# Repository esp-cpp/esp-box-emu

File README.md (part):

# esp-box-emu

<table style="padding:10px">
    <tr>
        <td></td>
        <td></td>
    </tr>
</table>

> A pocket-sized, Game Boy-style retro **emulation handheld** built around the
> ESP32-S3-BOX. Drop in a micro-SD card of ROMs and play NES, Game Boy / Color,
> Sega, MSX, and Genesis games — plus a full-speed port of **Doom** — on hardware
> you can 3D print and build yourself.

https://github.com/user-attachments/assets/2d3da6ea-2e80-42c3-bbd6-5a2c59601201

<!-- markdown-toc start - Don't edit this section. Run M-x markdown-toc-refresh-toc -->
**Table of Contents**

- [esp-box-emu](#esp-box-emu)
  - [Overview](#overview)
  - [Emulators](#emulators)
  - [Gallery](#gallery)
  - [Quick Start — Play It](#quick-start--play-it)
  - [Web Console](#web-console)
  - [Build the Hardware](#build-the-hardware)
  - [Build the Firmware](#build-the-firmware)
  - [ROMs and SD Card Setup](#roms-and-sd-card-setup)
    - [Boxart images](#boxart-images)
    - [metadata.csv format](#metadatacsv-format)
  - [Features and Roadmap](#features-and-roadmap)
  - [References and Inspiration](#references-and-inspiration)
  - [License](#license)

<!-- markdown-toc end -->

## Overview

The ESP-BOX-EMU turns an [ESP32-S3-BOX or
ESP32-S3-BOX-3](https://github.com/espressif/esp-box) into a handheld retro game
console. A custom add-on board and 3D-printed shell wrap the BOX in a Game Boy
Color form factor — real d-pad and buttons, battery, haptics, and a micro-SD
slot — and the firmware runs a stack of emulators behind a polished LVGL
interface with boxart, save states, and settings.

**Highlights**

- 🎮 **Six systems + Doom** — NES, Game Boy / Color, Sega Master System / Game
  Gear, Sega Genesis, and MSX 1/2 emulators, plus a full-speed **Doom** port —
  all with sound.
- 🧬 **Full-speed Genesis** — a custom **dual-core** port of gwenesis splits the
  emulation across both of the ESP32-S3's cores (CPU + video on one, the sound
  unit on the other) for full-speed Sega Genesis / Mega Drive *with* audio.
- ⚡ **No reboots** — every core and game loads on demand right from the menu, so
  you can jump between titles and even different systems without ever restarting
  the device.
- 🕹️ **Real controls** — d-pad, A/B/X/Y, Start/Select and volume buttons in a
  familiar Game Boy Color layout; the emulator is auto-selected from the ROM
  file extension.
- 💾 **Load from SD** — keep ROMs, boxart, and save states on a micro-SD card,
  and mount the card over USB-C as a mass-storage drive (TinyUSB MSC).
- 💤 **Save anywhere** — up to 5 save slots per game, each with an
  auto-generated screenshot shown in the load menu.
- 🔋 **Portable** — 1000 mAh LiPo battery with USB-C charging.
- 📳 **Haptics** — LRA haptic feedback (DRV2605), including in-game effects in
  Doom (weapon fire, taking damage, pickups, and more).
- 🖼️ **Polished UI** — LVGL menus for ROM select (with boxart) and settings
  (sound, brightness, display scaling, haptics), designed in Squareline Studio.
- 🌐 **Web console** — plug into a computer and Chrome or Edge offers a control
  panel: watch and play the screen, manage games and boxart, browse the SD
  card, change settings, and update the firmware, with nothing to install.
- 🛠️ **Fully open hardware** — 3D-printable GBC-style case and an open PCB
  (Fusion/Eagle **and** [atopile](https://atopile.io) + [KiCad](https://kicad.org)),
  all included in this repo.

## Emulators

The right emulator is chosen automatically from each ROM's file extension, and
games load on demand **straight from the menu — no reboot required**. Pick a
title, play, then drop back to the menu and launch a different game (or a
completely different system) without ever restarting the device. Every core runs
with audio, and several offer an **Unlocked mode** (toggle with the **X** button)
that removes the frame-rate cap for maximum speed.

| System | Core | Unlocked mode | Notes |
| --- | --- | :---: | --- |
| NES | [nofrendo](https://github.com/espressif/esp32-nesemu) | ✅ | D-Pad / A / B / Start / Select |
| Game Boy / Color | [gnuboy](https://github.com/rofl0r/gnuboy) | ✅ | D-Pad / A / B / Start / Select |
| Sega Master System / Game Gear | [smsplus](https://github.com/ekeeke/smsplus-gx) | ✅ | D-Pad / A / B / Start / Select |
| Sega Genesis / Mega Drive | [gwenesis](https://github.com/bzhxx/gwenesis) | — | Full speed with sound; 6-button pad (A→B, B→A, C→Y) |
| MSX 1 / 2 | [fmsx](https://fms.komkon.org/fMSX/) | — | D-Pad / A / B / Start / Select |
| Doom | [prboom](https://prboom.sourceforge.net/) | — | Full speed with audio **and haptic feedback** |
| Dark Forces | [The Force Engine](https://theforceengine.github.io/) (via [BSzili's Amiga port](https://github.com/BSzili/TheForceEngine/tree/amiga)) | — | Software renderer, iMuse sound effects and OPL3 music; see [Dark Forces setup](#dark-forces-setup) |
| PICO-8 | [femto8](https://github.com/benbaker76/femto8) | — | `.p8` and `.p8.png` carts; D-Pad, A/Y = O, B/X = X, START = PICO-8 pause menu; save states; cartdata saves to `pico8/cdata/`; see [PICO-8 setup](#pico-8-setup) |

Every core is a submodule ([esp-cpp/nofrendo](https://github.com/esp-cpp/nofrendo),
[gnuboy](https://github.com/esp-cpp/gnuboy), [smsplus](https://github.com/esp-cpp/smsplus),
[gwenesis](https://github.com/esp-cpp/gwenesis), [fmsx](https://github.com/esp-cpp/fmsx),
[prboom](https://github.com/esp-cpp/prboom), [TheForceEngine](https://github.com/esp-cpp/TheForceEngine),
[femto8](https://github.com/esp-cpp/femto8)): the core plus its `port/` glue to
`BoxEmu`, shared with [tab5-emu](https://github.com/esp-cpp/tab5-emu). Each
`components/<core>/CMakeLists.txt` here is the board's wrapper for it
(requirements, compile flags, linker fragment).

> 🧬 **Full-speed Genesis on the S3.** The Genesis core ships with a custom
> **dual-core** modification of gwenesis that spreads the workload across both of
> the ESP32-S3's CPU cores: **core 0** runs the 68000 CPU and VDP (video), while
> **core 1** runs the sound unit (Z80 + YM2612 FM synth + PSG). Sound-chip writes
> are queued and applied in order on core 1, which lets Genesis / Mega Drive
> games run at full speed *with* audio — something a single core can't keep up
> with.

<details>
<summary><strong>Doom controls and haptics</strong></summary>

**Controls:** **A** fire / enter · **B** strafe / backspace · **X** use ·
**Y** weapon toggle · **START** escape · **SELECT** map.

**Haptic feedback** is triggered when you fire a weapon (varies by weapon), take
damage (scaled to the health/armor lost), interact with something (e.g. a door),
or pick up a weapon, ammo, health, armor, a power-up, or a key / card.
</details>

<details>
<summary><strong>Dark Forces controls</strong></summary>

**In a mission:** **D-pad** move / turn · **A** fire · **B** jump · **X** use ·
**Y** next weapon · **START** escape menu. Hold **SELECT** as a modifier:
**SELECT + Left/Right** strafe · **SELECT + Down** crouch · **SELECT + Up**
automap · **SELECT + A** secondary fire · **SELECT + B** headlamp ·
**SELECT + X** gas mask · **SELECT + Y** previous weapon · **SELECT + START**
night vision. Running is always on.

**Menus, briefings and cutscenes:** the **D-pad** moves a virtual mouse cursor,
**A** clicks, **START** is Enter, **B** is Escape (skips cutscenes) and **Y** is
Space. Quitting from the game's escape menu returns to the emulator menu.

**Typing an agent name:** hold **SELECT**: **Right** adds a letter, **Up/Down**
change the last letter, **Left** deletes it; release SELECT and press **START**
to confirm.

The emulator's own pause menu (touch button or START+SELECT) still works for
video scaling and save slots; save slots only work while in a mission.
</details>

## Gallery

https://github.com/esp-cpp/esp-box-emu/assets/213467/3b77f6bd-4c42-417a-9eb7-a648f31b4008

https://github.com/esp-cpp/esp-box-emu/assets/213467/a3d18d03-c6a1-4911-89d1-e18119e8cc03

## Quick Start — Play It

Already have the add-on hardware (or an ESP32-S3-BOX you want to flash)? You
don't need to build anything from source — a prebuilt one-time **programmer** is
published with every release.

1. Download the `programmer` for your OS (`windows`, `macos`, or `linux`) from
   the latest [releases page](https://github.com/esp-cpp/esp-box-emu/releases).
2. Unzip it.
3. Run it: double-click the `.exe` on Windows, or run it from a terminal on
   macOS / Linux, e.g.:

   ```sh
   ./esp-box-emu_programmer_v1.0.0_macos.bin
   ```

   (The version in the filename matches the release you downloaded.)

Then [set up a micro-SD card](#roms-and-sd-card-setup) with your ROMs and you're
ready to play.

## Web Console

**Plug the emulator into a computer and it hands you a control panel.**
Connect the ESP-BOX-EMU's USB-C port to a computer running Chrome or Edge and
the browser pops up a notification pointing at
**[esp-cpp.github.io/esp-box-emu](https://esp-cpp.github.io/esp-box-emu/)**,
the firmware's WebUSB landing page. Click it, pick the emulator, and you're in:
no drivers, no app, no serial terminal. Watch the game being played,
take a screenshot, add a new game with its boxart, or update the firmware,
all from a browser tab.

What you can do from each tab:

- 📊 **Dashboard**: what's running right now (with its boxart), live frame-rate
  and memory graphs, the firmware and partition it booted from, why it last
  reset, and a button that hands the SD card to your PC as a USB drive.
- 🖥️ **Screen**: grab the game's (or the launcher's) screen, or turn on
  **Live** to keep it updating, and save it as a PNG. Play with the on-screen
  controller or your keyboard (arrows, Z / X / A / S, Enter = Start), save and
  load states in any slot, or quit the game.
- 📚 **Library**: every game on the card, grouped by console with its boxart
  and a game count per console. Search, filter by console (and, if you like,
  filter the handheld's launcher the same way), start any game with **Play**,
  or **Add a game**: drop in the ROM and a cover and the page uploads both and
  adds the line to `metadata.csv` for you. **Remove** takes one out again.
- 📁 **Files**: browse the SD card, download files, upload by drag and drop,
  create folders and delete things (handy for copying save states off the card).
- ⚙️ **Settings**: volume, mute, brightness, video scaling, resume last save
  and the haptic effect. The handheld's own menu shows each change right away,
  and it's saved to the card a moment later.
- 🔧 **System**: chip, flash, PSRAM, heap, ESP-IDF version, OTA state and the
  services on the link; restart the emulator (or into download mode for
  `idf.py flash`), and **Update firmware**, which restarts into the updater and
  opens the espp OTA console to send a new `build/esp-box-emu.bin`.
- 📜 **Console**: the device's log over Web Serial (pick the console's port),
  with a line filter, auto-follow, and save to a file.

**How it works:** the firmware's composite USB device includes a vendor
(WebUSB) interface that carries the same request/response link as
[`tools/emulink`](./tools/emulink), plus a USB descriptor that names the
landing page, which is how the browser knows where to send you. The page is
plain HTML, CSS and JavaScript modules in [`web/`](./web) (no build step),
published to GitHub Pages from `main`, and it talks to the device directly
from your browser; nothing goes through a server. Only one program can use the
link at a time, so close `emulink` (or the page) before switching between them.

Hacking on the page? Serve it locally with
`python3 -m http.server -d web 8000` and open http://localhost:8000 (WebUSB
needs https or localhost). See [`web/README.md`](./web/README.md) for the
details.

## Build the Hardware

The add-on is designed to match the Game Boy Color form factor and reuse GBC
button plastics and silicone membranes for an authentic feel. The shell is meant
to be 3D printed (PLA or PETG on a Prusa i3 mk3+) and assembled with M3 screws.

**Case / mechanical** — printable files are in [./mcad](./mcad) or on
[Printables](https://www.printables.com/model/396931-esp-box-emu). CAD is on
[Fusion 360 (free viewer)](https://a360.co/3le5oCQ):

**Electronics** — schematic and layout files are in [./ecad](./ecad), provided
as both Fusion/Eagle files and [atopile](https://atopile.io) +
[KiCad](https://kicad.org) sources. You can also order the board directly:

**GBC replacement buttons / membranes** used for a good play feel:

- [Silicone pads for Game Boy Color (1)](https://funnyplaying.com/collections/product/products/gbc-replacement-silicone-pads)
- [Silicone pads for Game Boy Color (2)](https://www.retromodding.com/products/game-boy-color-silicone-pads)
- [Game Boy Color button plastics](https://funnyplaying.com/collections/product/products/cgb-custom-buttons?variant=39333911920701)

## Build the Firmware

This repo uses submodules, so clone it recursively:

```sh
git clone --recurse-submodules git@github.com:esp-cpp/esp-box-emu
```

If you already cloned it non-recursively (or forgot the flag), pull the
submodules with:

```sh
git submodule update --init --recursive
```

Then build, flash, and open the serial monitor with [ESP-IDF](https://docs.espressif.com/projects/esp-idf/en/latest/esp32s3/get-started/index.html):

```sh
idf.py -C updater build   # once: the updater app, which goes in ota_1
idf.py -p PORT flash monitor
```

The updater (`updater/`) is what over-USB updates (`tools/emulink`) reboot
into, and what a bad update rolls back to, so build it before the first
flash: the emulator's `idf.py flash` then writes both. After that, updates
can go over USB with `emulink ota`.

Replace `PORT` with your board's serial port. To exit the monitor, type
`Ctrl-]`.

### Measuring performance and memory

The firmware prints greppable one-line reports on the serial console so a
captured play session doubles as a profile:

- `[mem] phase=boot|menu|launch|quit ...` — internal RAM / PSRAM free and
  largest free block at each phase, with `[mem] delta ...` lines at launch and
  quit relative to the menu (a non-zero delta after quitting is a leak or
  fragmentation).
- `[mem] block|region|task phase=...` — at boot and launch, every internal-RAM
  block above a threshold (labelled with the task whose stack it is), each
  registered heap region's used/free/largest, and every task's stack high-water
  mark (`stack_free_min`, repeated at quit after a full play session).
- `[genesis mem] NAME: N bytes -> INTERNAL|PSRAM` — where each big emulator
  buffer landed (the Genesis gets noticeably slower when its hot buffers fall
  back to PSRAM).
- `[genesis perf] fps=.. frame=..us 68k=..us vdp=..us convert=..us barrier=..us ...` —
  per-frame time breakdown averaged over the last 300 frames (~5 s): 68000,
  VDP render, RGB565 conversion, time core 0 spends waiting for the core-1
  sound unit, present/audio, pacing sleep, `late=`/`skipped=`/`dropped=`
  frame counts (skipped = emulated without rendering because the panel could
  not show the frame), `blit=` (video task time per displayed frame), the
  core-1 sound unit's own frame time, and Z80 counters (`irq=` V-ints taken,
  `busreq=`, `halted=` scanline slices lost to a held bus, `wto=` handshake
  timeouts, `ymw=` Z80→YM2612 writes). Compile with `GENESIS_PERF=0` to
  remove it.
- `[display] lcd spi clock: N Hz` — the clock the LCD SPI device actually got
  (the ESP32-S3 can only divide 80 MHz by integers, so a 60 MHz request runs
  at 40 MHz: 320×240×16bpp is ~31 ms per frame, the panel's ~31 fps ceiling).

Capture and summarise a session (performance PRs should include a before/after
from the same game and the same ~1 minute of play):

```sh
python tools/serial_capture.py PORT --out before.log --until "delta phase=quit"
# ... flash the change, play the same section again ...
python tools/serial_capture.py PORT --out after.log --until "delta phase=quit"
python tools/perf_report.py before.log after.log
```

`perf_report.py` prints each run's launch/quit memory, buffer placement, and
the perf-line averages side by side with deltas.

## ROMs and SD Card Setup

Format a micro-SD card as **FAT** and add your ROMs (`.nes`, `.gb`, `.gbc`, …),
boxart images (`.jpg`), and a `metadata.csv` file (see the example
[metadata.csv](./metadata.csv)).

### Boxart images

Boxart displays best at 100 px wide. The
[./boxart/source/resize.bash](./boxart/source/resize.bash) script resizes every
`.jpg` in `boxart/source` to 100 px wide (preserving aspect ratio) and writes the
results to the `boxart` folder. Copy those onto the SD card and reference them
from your metadata file.

### Dark Forces setup

Dark Forces is played with the original (purchased) game data; the engine does
not include it. Copy the DOS install files onto the SD card into a single
folder, for example `darkforces/`:

```
darkforces/DARK.GOB
darkforces/SOUNDS.GOB
darkforces/SPRITES.GOB
darkforces/TEXTURES.GOB
darkforces/LFD/*.LFD       (menus, briefings and cutscenes)
```

Then reference `DARK.GOB` from `metadata.csv`:

```csv
darkforces/DARK.GOB, boxart/darkforces.jpg, Star Wars: Dark Forces
```

Settings (`settings.ini`) and agent / save files are written to the same folder.

### PICO-8 setup

PICO-8 carts are plain `.p8` text files or `.p8.png` cartridge images. Put them
in a folder on the card (for example `pico8/`) and reference them from
`metadata.csv`:

```csv
pico8/celeste.p8, boxart/celeste.jpg, Celeste Classic
```

Carts that use `cartdata()` save to `pico8/cdata/`. The 128x128 screen shows
1:1 in the "original" video mode and scaled to 240x240 in "fit". Multi-cart
games that `load("#id")` their other carts work when those carts sit in the
same folder as `id.p8.png` / `id.p8`.

What to expect: the Lua interpreter runs at roughly 1.3M instructions per
second on the S3 (its heap lives in PSRAM), enough for carts of Celeste's
weight at full speed, but CPU-heavy carts close to PICO-8's limit run at a
few frames per second. Save states work (the cart's Lua heap and PICO-8
RAM are snapshotted between frames); carts' own `cartdata()` saves are kept
separately; there is no mouse or keyboard.

### metadata.csv format

Each line maps a ROM to its boxart and display name:

```csv
<rom filename>, <rom boxart filename>, <rom display name>
```

Example:

```csv
mario.nes, boxart/mario.jpg, Mario Bros.
super_mario_1.nes, boxart/super_mario_bros_1.jpg, Super Mario Bros.
super_mario_3.nes, boxart/super_mario_bros_3.jpg, Super Mario Bros. 3
zelda.nes, boxart/zelda1.jpg, The Legend of Zelda
zelda_2.nes, boxart/zelda2.jpg, The Legend of Zelda 2: the Adventure of Link
mega_man.nes, boxart/megaman1.jpg, MegaMan
metroid.nes, boxart/metroid1.jpg, Metroid
pokemon_blue.gb, boxart/pokemon_blue.jpg, Pokemon Blue
pokemon_red.gb, boxart/pokemon_red.jpg, Pokemon Red
pokemon_yellow.gbc, boxart/pokemon_yellow.jpg, Pokemon Yellow
links_awakening.gb, boxart/tloz_links_awakening.jpg, The Legend of Zelda: Link's Awakening
links_awakening.gbc, boxart/tloz_links_awakening_dx.jpg, The Legend of Zelda: Link's Awakening DX
```

## Features and Roadmap

A checklist of what's implemented and what's still in progress.

**Emulation**

- [x] Auto-select emulator by ROM extension: NES, GB/GBC, SMS/GG, MSX, Genesis, Doom, Dark Forces, PICO-8
- [x] On-demand core loading — every emulator and game loads at runtime with no reboot needed to switch games or systems
- [x] Custom **dual-core Genesis** (gwenesis): 68000 + VDP on one ESP32-S3 core, sound unit (Z80 + YM2612 + PSG) on the other, for full-speed audio and gameplay
- [x] Doom haptic feedback :rocket:
- [x] Save state (with automatic save-screenshot creation to the SD card)
- [x] Load state — up to 5 slots per game, with save-screenshot previews
- [x] Shared-memory system so many emulators can be built in together while keeping their hot state in fast internal RAM
- [x] Dark Forces (The Force Engine port; software renderer with sound and music)
- [ ] SNES emulator (WIP)

**User interface**

- [x] LVGL ROM-select menu with boxart and title, navigable by controller
- [x] Games grouped by console: left / right jump to the previous / next
  console, and the console in the header (tap it, or press X) opens a picker
  that shows only one console's games (outlined while filtered; `emulink
  filter <console>` over USB)
- [x] LVGL settings menu (volume, video, haptics) and in-game pause menu
- [x] GUI data (titles + boxart) loaded from the [metadata file](./metadata.csv)
- [x] Squareline Studio source for the LVGL boilerplate ([SLS files](./squareline), [generated files](./components/gui/generated))

**Video and audio**

- [x] Emulator framebuffers in SPIRAM, with queued screen transfers for maximum draw speed
- [x] Video scaling with ORIGINAL, FIT, and FILL display modes
- [x] Audio output over I2S via the es8311 codec ([codec component](./components/codec))
- [x] Mute button toggles audio while a ROM is running
- [x] Haptic feedback via a DRV2605-driven LRA
- [ ] Decorative graphics in the black borders during NES / GB/C emulation (WIP)

**Storage and input**

- [x] micro-SD (FAT) filesystem over SPI
- [x] TinyUSB MSC device to expose the SD card to an attached USB host
- [x] Memory-mapping of the selected ROM from storage into a raw data partition (SPI flash)
- [x] D-pad + A/B/X/Y + Start/Select input (MCP23x17 on v0 hardware, AW9523 on v1)
- [x] Touchscreen input ([tt21100 component](./components/tt21100))

**Hardware**

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
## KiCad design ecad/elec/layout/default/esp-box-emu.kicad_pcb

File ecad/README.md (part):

# ESP-BOX-EMU ecad

This folder contains the electronic design of the ESP-BOX-EMU.

The ESP-BOX-EMU contains a single circuit board with the following components:
- USB-C connector
- Conductive / Membrane switches for d-pad, abxy, and start/select buttons which mate with GBC membranes and buttons
- Tactile switches for Volume +/-
- RED LED for charging indication
- DRV2605L haptic driver
- JST-PH connector for the LiPo battery
- AW9523 I/O expander
- MCP73831 LiPo charger
- MAX17048 LiPo state-of-charge monitor (I2C)
- MicroSD card slot
- TPS63020 5V buck-boost converter (battery -> 5V for the box)

These features are supported in two different versions of the electronics, targeting:
- ESP32-S3-Box
- ESP32-S3-Box-3

## Layout of this folder

- `elec/src/` - atopile sources (modern atopile >= 0.15 syntax)
- `elec/src/parts/` - atomic parts (auto-generated from LCSC plus local
  custom parts for the GBC membranes/buttons, board outlines and edge fingers)
- `elec/layout/` - KiCad layouts, one folder per build (netlist-synced by
  `ato build`; placement/routing edits are preserved)
- `scripts/` - layout automation (MCAD position export, scripted placement,
  base/connector layout sync)
- `Box Electronics v*.sch/brd`, `Box-3 Electronics v*.sch/brd` - the
  Fusion 360 / Eagle design the boards were actually manufactured from

The pre-migration atopile 0.2 sources, the old shared footprint library and
the old routed KiCad-6 boards were removed after the 0.15 migration; they
are available in git history (pre-2026-07) if ever needed.

## Setup

``` sh
# one time steps on your machine (any of these; uv shown)
uv tool install --python 3.14 atopile
```

Dependencies (e.g. `atopile/ti-tps63020`) are fetched automatically into
`.ato/modules/` on first build; `ato add <package>` adds new ones.

## Build

``` sh
# build everything
ato build

# build for ESP32-S3-BOX
ato build -b box-emu

# build for ESP32-S3-BOX-3
ato build -b box-3-emu
```

### Offline build (atopile 0.16 service migration)

As part of atopile's 0.16 platform migration (services moving from
`*.atopileapi.com` / `packages.atopile.io` to `app.atopile.io`), the hosted
components-picker API used by the 0.15.x CLI
(`components.atopileapi.com`) was taken offline, and no public replacement
endpoint exists for the CLI yet. Until atopile publishes a CLI that speaks
to the new services, build via the local stand-in server, which answers
picker queries from the part data already pinned in this repo:

``` sh
scripts/ato-build-offline.sh                 # all targets
scripts/ato-build-offline.sh -b box-emu-base # one target
```

Two caveats:

- Footprints/symbols still come from `build/cache/parts/easyeda/` (or the
  still-alive EasyEDA API). If the cache is stale (>1 day old), refresh the
  `atopile_queried_at` stamps inside the cached `C*.json` files rather than
  hammering EasyEDA's rate limiter with re-downloads.
- The stand-in returns no part *attributes*, so builds rewrite the hidden
  parameter annotations in the layouts to the design constraints (e.g. a
  resistor annotated `10kΩ ±1%` from the real part data becomes `±5%` from
  the design). The picked LCSC parts, BOM and copper are unchanged; a
  normal online build will restore the exact annotations once the service
  returns.

## Continuous integration

`.github/workflows/atopile.yml` (official `atopile/setup-atopile@v2` action)
builds every target from the checked-in sources with
`ato build --keep-picked-parts --keep-net-names --keep-designators`, then
runs `scripts/canonicalize-boards.py --all` and fails if `git diff` shows
any change to `elec/layout` or `elec/src` -- i.e. the checked-in design
must be exactly reproducible. (We don't use `ato build --frozen`: atopile
0.15.x writes KiCad group member lists in nondeterministic order, which
makes frozen flaky; the canonicalize+diff check gives the same guarantee
robustly.) It then exports gerbers, pick & place, BOM, STEP, GLB and a
rendered PNG for `box-emu` and `box-3-emu` (`-t all -t 3d-image`), plus
top/bottom PDFs via the kicad-cli bundled in the atopile container.
Artifacts are uploaded per board and attached to releases as zips.

Two reproducibility rules this relies on:

- **Parts are pinned.** None of the part `.ato` files carry the
  `is_auto_generated` trait: atopile would otherwise re-download every
  picked part from the EasyEDA API on each build and *replace* the
  checked-in part directory whenever the API response differs (which it
  does between regions, over time, and during their frequent partial
  outages). Without the trait, atopile logs "not overwriting" and the
  repo stays the source of truth. To intentionally update a part, delete
  its directory and re-run `ato create part --search <LCSC>`.
- **After local layout sessions**, run `ato build` +
  `python3 scripts/canonicalize-boards.py --all` and commit the result,
  so CI's rebuild matches byte-for-byte.

The LCSC/EasyEDA API has multi-hour outages; build steps retry, but a
run during a hard outage will still fail at part picking -- just re-run
it later.

## Ordering / manufacturing notes

**Surface finish: order ENIG, not HASL.** The GBC button footprints expose
bare-copper interdigitated fingers that the carbon membrane pucks press
against. With HASL those fingers come back coated in solder (uneven, prone
to oxidation) and the buttons work poorly; with ENIG they come back flat
gold, which is the standard finish for carbon-contact keypads. This is a
per-order fab option (JLCPCB: "Surface Finish" -> "ENIG") and cannot be
enforced from the design files.

Related, already handled in the footprints: the buttons' four corner
connection pads are tented (copper-only, no paste, no mask opening), so
PCBA assembly applies no solder anywhere on the button contact areas. If
you regenerate or edit `GBC_*_BUTTON` footprints, keep the pads
`(layers "F.Cu")` only.

## Working on the KiCad layouts

Each build owns one board file: `elec/layout/<build>/<build>.kicad_pcb`
(KiCad 9+ format; there is no `.kicad_pro` — open the `.kicad_pcb` directly
in KiCad's PCB Editor). The `fp-lib-table` next to each board resolves all
footprints from the atomic parts in `elec/src/parts/`, so the boards are
self-contained as long as the repo layout is intact.

The `.ato` sources are the source of truth for everything electrical;
KiCad is only for placement and routing:

``` sh
# build a target and open its layout in KiCad in one step
ato build -b box-3-emu --open

# or open it manually
open "elec/layout/box-3-emu/box-3-emu.kicad_pcb"
```

The edit loop:

1. Change schematics by editing the `.ato` files (never add/remove
   components or change connectivity in KiCad — the next build will
   revert it).
2. Run `ato build -b <build>`. This syncs footprints and nets into the
   board file. Footprints are matched by their `atopile_address` property,
   so your existing placement and routing are preserved; new components
   appear stacked near the origin for you to place.
3. Place/route in KiCad and save. **Close the board (or at least save it)
   before the next `ato build`** — atopile rewrites the file on disk, and
   KiCad's PCB editor will not auto-reload; reopen the file after each
   build. A stale `~<name>.kicad_pcb.lck` file means KiCad still has it
   open.

Useful flags when iterating on layout: `--keep-designators`,
`--keep-net-names`, and `--keep-picked-parts` take those from the existing
PCB instead of regenerating them, and `--frozen` fails the build if the
PCB would change at all (good for CI).

Recovering from common accidents:

- **Deleted a footprint in KiCad?** Harmless to the design -- the `.ato`
  source is the source of truth, and the next `ato build -b <build>`
  re-adds it (near the origin; its placement is lost, its part gets
  re-picked). Restore known positions with `place-parts.py apply` if it
  was a mechanically-placed part. It's worth running
  `place-parts.py dump` into `positions.json` after every good layout
  session (and committing it) so *every* part's placement has a snapshot.
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
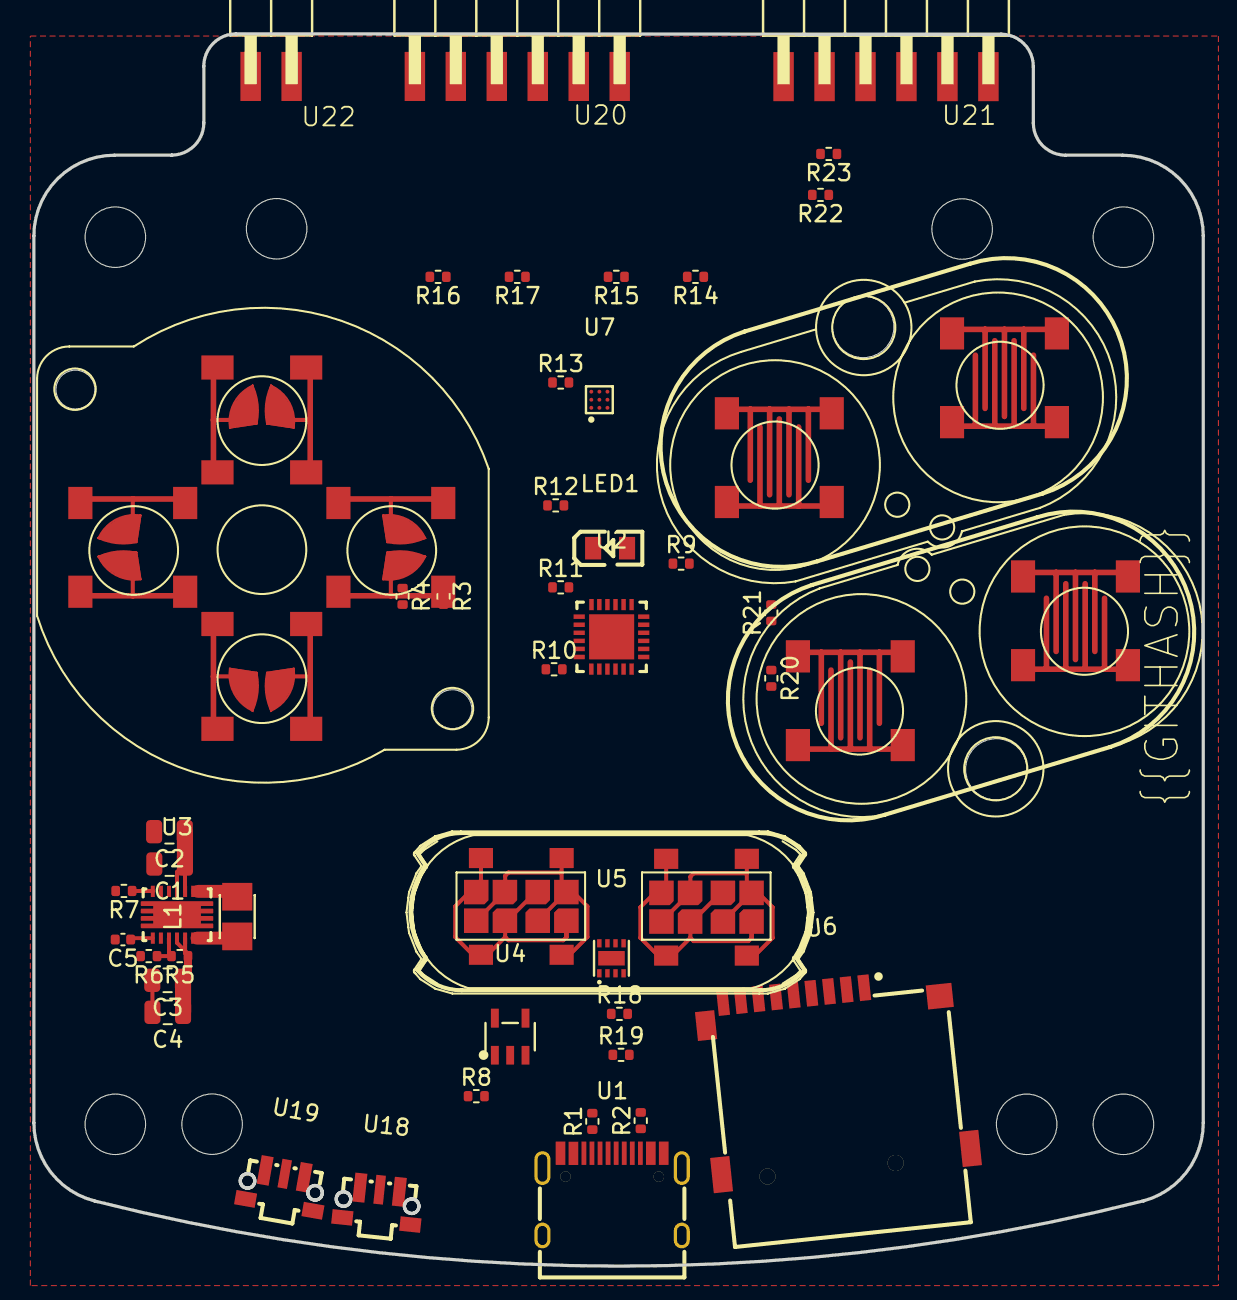
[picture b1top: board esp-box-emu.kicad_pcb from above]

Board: 2 copper layers, 72.5 x 76.4 mm, 64 parts (0 on the bottom side), 39 nets.

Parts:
@HOLE0, @HOLE1, @HOLE2, @HOLE3, @HOLE4, @HOLE5, @HOLE6, @HOLE7: (no value)
C1, C2, C3, C4: 25V 10uF X5R ±10% 0805 Multilayer Ceramic Capacit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; C0805
C5: 16V 100nF X7R ±10% 0402 Multilayer Ceramic Capaci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; C0402
L1: IND-SMD_L2.5-W2.0_WPN252012H
LED1: LED0805-R-RD
R1, R2: 62.5mW Thick Film Resistors 50V ±100ppm/℃ ±1% 4.7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; R0402
R3, R4, R10, R11, R12, R13, R14, R15, R16, R17, R18, R19, R20, R21: 62.5mW Thick Film Resistors 50V ±100ppm/℃ ±1% 10k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; R0402
R5: 62.5mW Thick Film Resistors 50V ±100ppm/℃ ±1% 243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; R0402
R6: 62.5mW Thick Film Resistors 50V ±100ppm/℃ ±0.5% 2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; R0402
R7: 62.5mW Thick Film Resistors 50V ±100ppm/℃ ±1% 1MΩ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; R0402
R8: 62.5mW Thick Film Resistors 50V ±100ppm/℃ ±1% 2kΩ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; R0402
R9: 62.5mW Thick Film Resistors 50V ±100ppm/℃ ±1% 2.5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; R0402
R22: 62.5mW Thick Film Resistors 50V ±100ppm/℃ ±1% 255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; R0402
R23: 62.5mW Thick Film Resistors 75V ±1% ±100ppm/℃ 249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; R0402
U1: USB-C-SMD_TYPE-611-T3-W
U2: VFQFPN-24_L4.0-W4.0-P0.50-BL-EP2.8
U3: VSON-14_L4.0-W3.0-P0.50-BL-EP_TI_DSJ
U4: SOT-23-5_L3.0-W1.7-P0.95-LS2.8-BL
U5: DFN-8_L2.0-W2.0-P0.50-BL-EP
U6: SIM-SMD_C9900007362
U7: DSBGA-9_L1.5-W1.5-R3-C3-P0.50-BL
U8, U9, U10, U11: GBC_DPAD_BUTTON
U12, U13, U14, U15: GBC_A_B_BUTTON
U16, U17: GBC_START_SELECT_BUTTON
U18, U19: SW-SMD_E-SWITCH_TL3340
U20, U21: 2X06_EDGE_REVERSED
U22: 2X02_EDGE_REVERSED
U$1: SILKSCREENGBC_D-PAD; GAMEBOY_COLOR_DPAD_SILK
U$2: SILKSCREENGBC_START/SELECT; GAMEBOY_COLOR_START_SELECT_SILK
U$3, U$4: SILKSCREENGBC_A/B; GAMEBOY_COLOR_A_B_BUTTON_MEMBRANE

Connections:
battery_measurement: R22.2, R23.1, U21.8
cathode: LED1.1, R9.1
cc1: R1.1, U1.A5
cc2: R2.1, U1.B5
cs: U6.2, U21.1
dm: U1.A7, U1.B7, U20.5
dp: U1.A6, U1.B6, U20.7
gnd: C1.2, C2.2, C3.2, C4.2, C5.2, R1.2, R2.2, R6.2, R7.2, R8.2, R10.1, R11.1, R12.1, R13.1, R14.1, R15.1, R16.1, R17.1, R18.1, R19.1, R20.1, R21.1, R23.2, U1.17, U1.18, U1.19, U1.20, U1.A1, U1.A12, U1.B1, U1.B12, U2.9, U2.25, U3.2, U3.13, U3.15, U4.2, U5.4, U6.6, U20.9, U20.10, U21.9, U21.10, U22.2, U22.3
l1: L1.1, U3.8, U3.9
l2: L1.2, U3.6, U3.7
mcp73831-gnd: R9.2, U4.1
miso: U6.7, U21.5
mosi: U6.3, U21.3
out: R5.2, R6.1, U3.3
p0_0: R10.2, U2.5, U8.1, U8.3
p0_1: R11.2, U2.6, U9.1, U9.3
p0_2: R12.2, U2.7, U10.1, U10.3
p0_3: R13.2, U2.8, U11.1, U11.3
p0_4: R14.2, U2.10, U12.1, U12.3
p0_5: R15.2, U2.11, U13.1, U13.3
p0_6: R16.2, U2.12, U14.1, U14.3
p0_7: R17.2, U2.13, U15.1, U15.3
p1_0: R18.2, U2.1, U16.1, U16.3
p1_1: R19.2, U2.2, U17.1, U17.3
p1_2: R20.2, U2.3, U18.1
p1_3: R21.2, U2.4, U19.1
p1_4: U2.14, U5.5
pg: R7.1, U3.14
prog: R8.1, U4.5
sck: U6.5, U21.7
scl: R4.1, U2.19, U5.7, U20.6
sda: R3.1, U2.20, U5.8, U20.8
vcc: R3.2, R4.2, U2.21, U6.4, U8.2, U8.4, U9.2, U9.4, U10.2, U10.4, U11.2, U11.4, U12.2, U12.4, U13.2, U13.4, U14.2, U14.4, U15.2, U15.4, U16.2, U16.4, U17.2, U17.4, U18.2, U18.3, U19.2, U19.3, U20.11, U20.12, U21.11, U21.12
vcc-1: C3.1, C4.1, R5.1, U3.4, U3.5, U22.1, U22.4
vcc-2: C1.1, C2.1, LED1.2, R22.1, U3.10, U3.11, U4.3, U5.2, U5.3
vcc-3: U1.A4, U1.A9, U1.B4, U1.B9, U4.4
vina: C5.1, U3.1, U3.12
vol_down.btn.btn-_4: U19.4, U19.5
vol_up.btn.btn-_4: U18.4, U18.5

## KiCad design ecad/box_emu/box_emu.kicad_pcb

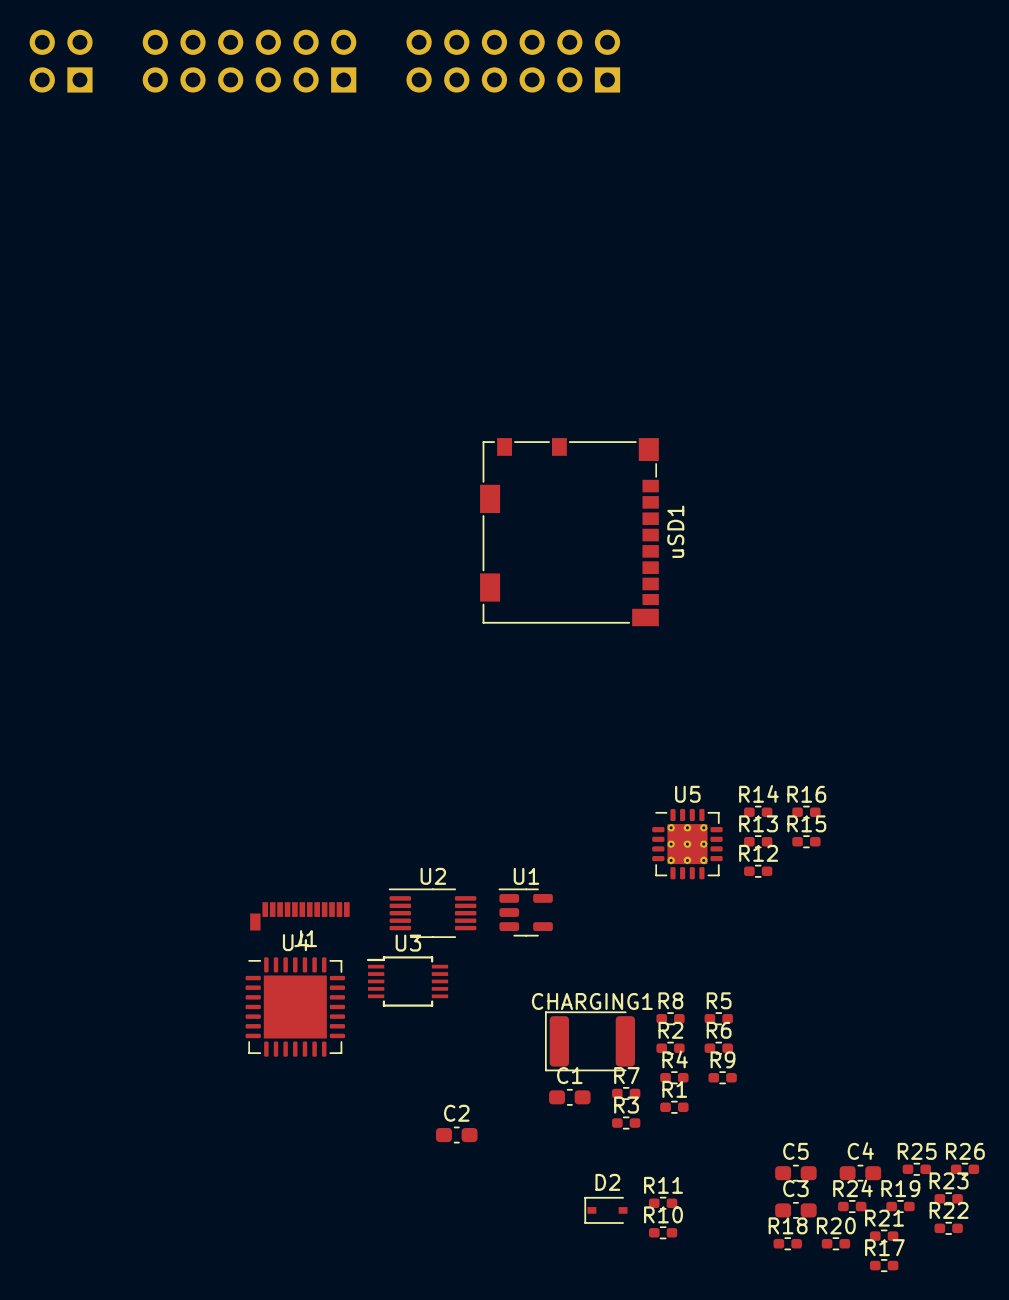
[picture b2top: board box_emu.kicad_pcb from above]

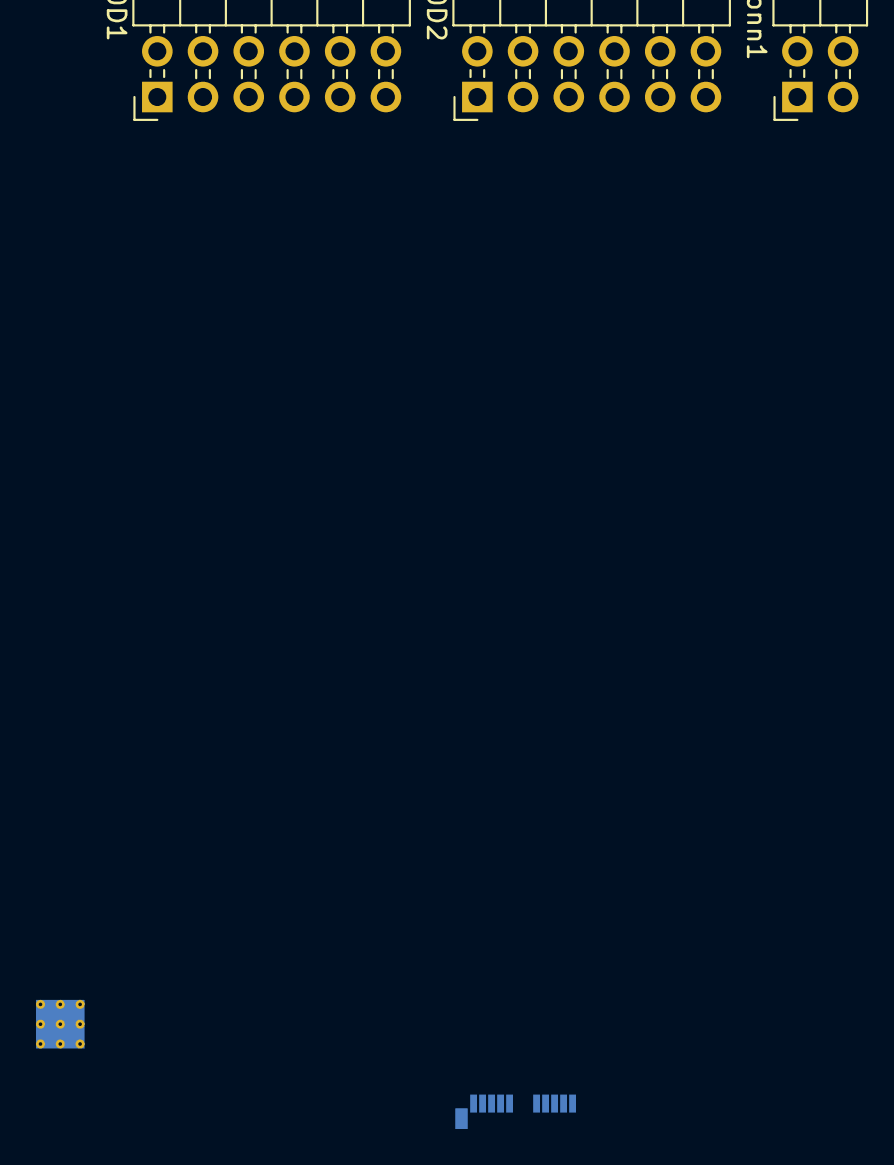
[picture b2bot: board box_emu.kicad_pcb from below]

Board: 2 copper layers, 43 parts (3 on the bottom side), 37 nets, no tracks yet.

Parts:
5V_Conn1: Conn_02x02_Counter_Clockwise; PinHeader_2x02_P2.54mm_Horizontal
C1, C4: 10uF; C_0603_1608Metric_Pad1.08x0.95mm_HandSolder
C2: 1uF; C_0603_1608Metric_Pad1.08x0.95mm_HandSolder
C3: .1uF; C_0603_1608Metric_Pad1.08x0.95mm_HandSolder
C5: 2.2uF; C_0603_1608Metric_Pad1.08x0.95mm_HandSolder
CHARGING1: LED; LED_1812_4532Metric_Pad1.30x3.40mm_HandSolder
D2: NSR0340HT1G; D_SOD-323
J1: USB_C_Receptacle_USB2.0; USB_C_Plug_Molex_105444
PMOD1, PMOD2: Conn_02x06_Top_Bottom; PinHeader_2x06_P2.54mm_Horizontal
R1: 2.0K; R_0402_1005Metric_Pad0.72x0.64mm_HandSolder
R2, R10, R11: 5.1K; R_0402_1005Metric_Pad0.72x0.64mm_HandSolder
R3, R4, R5, R6, R7, R8, R9, R17, R18, R19, R20, R21, R22, R23, R24, R25, R26: 10K; R_0402_1005Metric_Pad0.72x0.64mm_HandSolder
R12: 1.87M; R_0402_1005Metric_Pad0.72x0.64mm_HandSolder
R13: 340K; R_0402_1005Metric_Pad0.72x0.64mm_HandSolder
R14, R16: 200K; R_0402_1005Metric_Pad0.72x0.64mm_HandSolder
R15: 1.8M; R_0402_1005Metric_Pad0.72x0.64mm_HandSolder
U1: MCP73831-2-OT; SOT-23-5
U2: DRV2605LDGS; VSSOP-10_3x3mm_P0.5mm
U3: ADS1015IDGS; TSSOP-10_3x3mm_P0.5mm
U4: MCP23017_ML; QFN-28-1EP_6x6mm_P0.65mm_EP4.25x4.25mm
U5: TPS61092; Texas_S-PVQFN-N16_EP2.7x2.7mm_ThermalVias
uSD1: Micro_SD_Card_Det; microSD_HC_Molex_104031-0811

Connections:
+3.3V: 5V_Conn1.2, 5V_Conn1.4, C1.2, C2.2, C3.2, C4.2, C5.2, J1.A1 (GND), J1.A12 (GND), J1.B1 (GND), J1.B12 (GND), J1.S1 (SHIELD), PMOD1.5, PMOD1.6, PMOD1.11, PMOD1.12, PMOD2.5, PMOD2.6, PMOD2.11, PMOD2.12, R1.2, R3.1, R4.1, R5.1, R6.1, R7.2, R8.1, R9.2, R10.1, R11.2, R13.2, R16.2, R17.1, R18.1, R19.1, R20.1, R21.1, R22.1, R23.1, R24.1, R25.1, R26.1, U1.2 (VSS), U2.5 (EN), U2.8 (GND), U2.10 (VDD), U3.3 (GND), U3.8 (VDD), U4.5 (VDD), U4.6 (VSS), U4.29 (EP), U5.5 (PGND), U5.6 (PGND), U5.7 (PGND), U5.10 (SYNC), U5.13 (GND), U5.17 (PAD), uSD1.4 (VDD), uSD1.6 (VSS), uSD1.11 (SHIELD)
+5V: 5V_Conn1.1, 5V_Conn1.3, C5.1, D2.1 (K), R15.1, U5.1 (VOUT), U5.15 (VOUT), U5.16 (VOUT)
+BATT: C1.1, C3.1, C4.1, R12.1, R14.1, U1.3 (VBAT), U5.8 (VBAT)
/A: R23.2, U4.21 (GPA4)
/B: R24.2, U4.22 (GPA5)
/CLK: PMOD2.4, uSD1.5 (CLK)
/CS: PMOD2.1, uSD1.2 (DAT3/CD)
/DOWN: R18.2, U4.18 (GPA1)
/ENABLE: R14.2, U5.11 (EN)
/LEFT: R21.2, U4.19 (GPA2)
/RIGHT: R20.2, U4.20 (GPA3)
/SCL: PMOD1.9, R3.2, U2.2 (SCL), U3.10 (SCL), U4.8 (SCK)
/SDA: PMOD1.10, R4.2, U2.3 (SDA), U3.9 (SDA), U4.9 (SDA)
/SELECT: R22.2, U4.26 (GPB1)
/SI: PMOD2.2, uSD1.3 (CMD)
/SO: PMOD2.3, uSD1.7 (DAT0)
/START: R19.2, U4.25 (GPB0)
/UP: R17.2, U4.17 (GPA0)
/USB D+: J1.A6 (D+), PMOD1.4
/USB D-: J1.A7 (D-), PMOD1.3
/X: R25.2, U4.23 (GPA6)
/Y: R26.2, U4.24 (GPA7)
unnamed: C2.1, U2.1 (REG)
unnamed: CHARGING1.1 (K), R2.1
unnamed: J1.A5 (CC1), R11.1
unnamed: J1.B5 (CC2), R10.2
unnamed: U5.3 (SW), U5.4 (SW)
unnamed: R1.1, U1.5 (PROG)
unnamed: R2.2, U1.1 (STAT)
unnamed: R5.2, U4.13 (A2)
unnamed: R6.2, U4.12 (A1)
unnamed: R7.1, U4.14 (~RESET)
unnamed: R8.2, U4.11 (A0)
unnamed: R9.1, U3.1 (ADDR)
unnamed: R12.2, R13.1, U5.9 (LBI)
unnamed: R15.2, R16.1, U5.14 (FB)
VBUS: CHARGING1.2 (A), D2.2 (A), J1.A4 (VBUS), J1.A9 (VBUS), J1.B4 (VBUS), J1.B9 (VBUS), U1.4 (VDD)

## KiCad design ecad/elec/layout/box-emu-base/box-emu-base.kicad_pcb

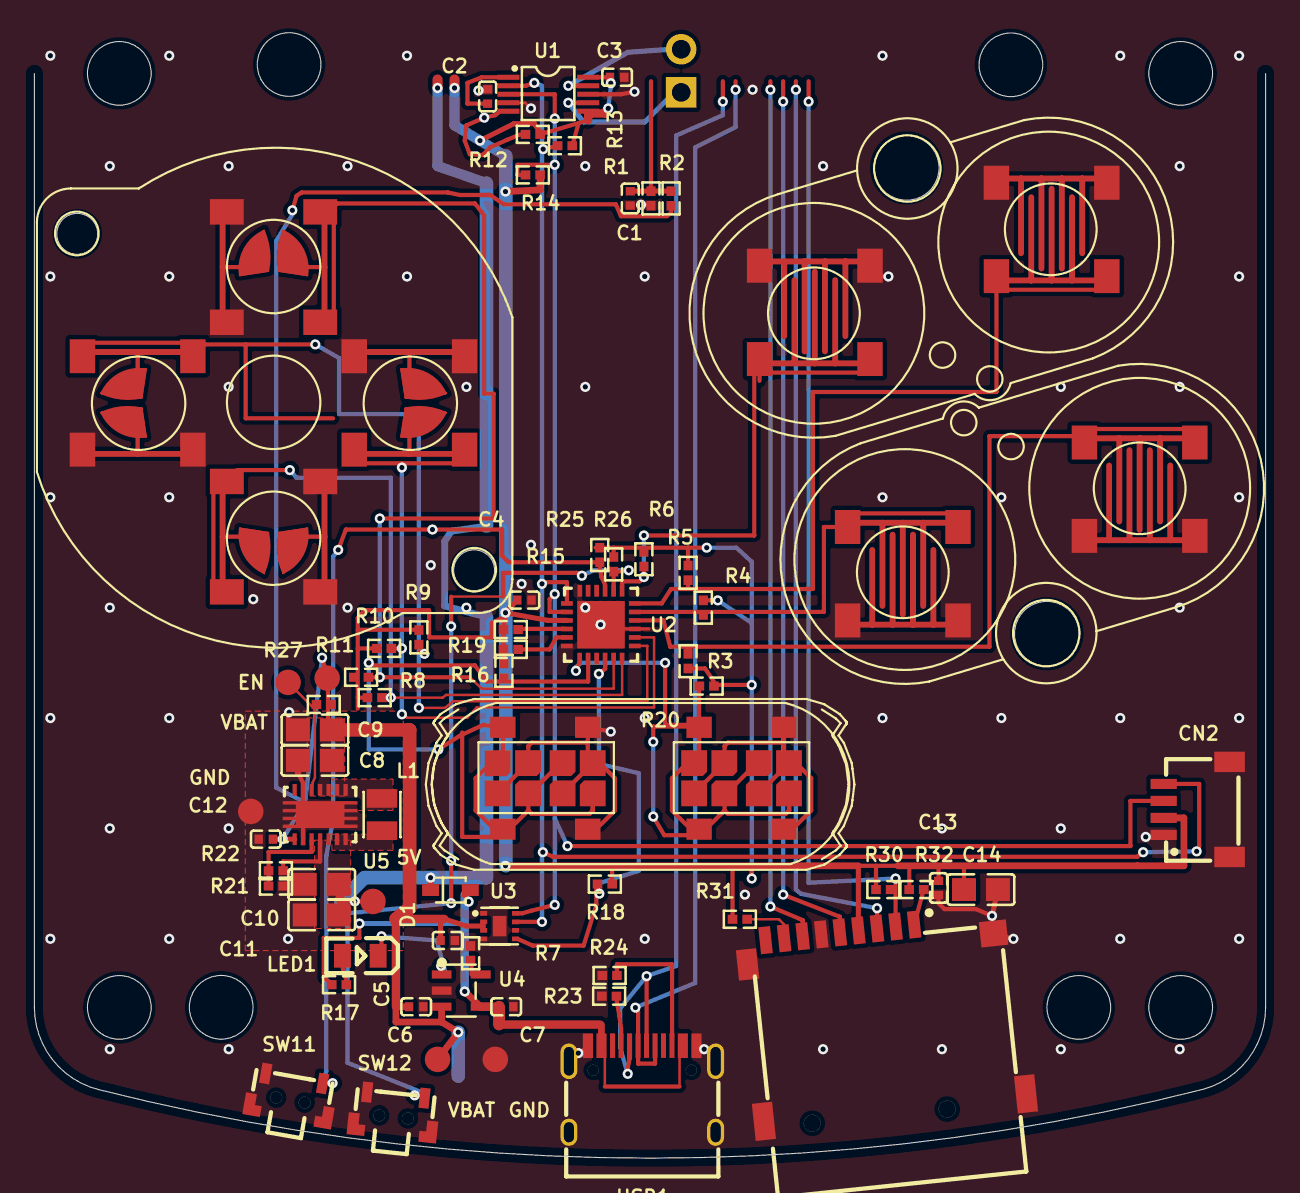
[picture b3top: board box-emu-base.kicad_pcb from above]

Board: 2 copper layers, 79 parts (1 on the bottom side), 41 nets.

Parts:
C1, C3, C4, C5, C13: 100nF ±10%; C0402
C2: 1µF ±20%; C0402
C6, C7: 4.7µF ±10%; C0402
C8, C9: 10µF ±20%; C0805
C10, C11, C14: 22µF ±20%; C0805
C12: 100nF ±20%; C0402
CN1: CONN-SMD_P2.00_S2B-PH-SM4-TB-LF-SN
CN2: CONN-SMD_4P-P1.00_SM04B-SRSS-TB-LF-SN
D1: SOD-323_L1.8-W1.3-LS2.5-RD
H1: HDR-TH_2P-P2.54-V-M-1
L1: IND-SMD_L2.5-W2.0_WPN252012H
LED1: LED0805-R-RD
MECH1, MECH2: GAMEBOY_COLOR_A_B_BUTTON_MEMBRANE
R1, R2: 1MΩ ±1%; R0402
R3, R4, R5, R6, R8, R9, R10, R11, R12, R13, R14, R15, R16, R18, R19, R20, R25, R26, R27, R30, R31, R32: 10kΩ ±5%; R0402
R7: 2kΩ ±5%; R0402
R17, R23, R24: 5.1kΩ ±5%; R0402
R21: 91kΩ ±1%; R0402
R22: 820kΩ ±1%; R0402
SW1, SW2, SW3, SW4: GBC_A_B_BUTTON
SW5, SW6, SW7, SW8: GBC_DPAD_BUTTON
SW9, SW10: GBC_START_SELECT_BUTTON
SW11, SW12: SW-SMD_2P-TS24CA
TP1, TP2, TP3, TP4, TP5, TP6: TESTPOINT
U1: VSSOP-10_L3.0-W3.0-P0.50-LS4.9-BL
U2: VFQFPN-24_L4.0-W4.0-P0.50-BL-EP2.8
U3: TDFN-8_L2.0-W2.0-P0.50-BL-EP1.2
U4: SOT-23-5_L3.0-W1.7-P0.95-LS2.8-BL
U5: VSON-14_L4.0-W3.0-P0.50-BL-EP_TI_DSJ
U6: SIM-SMD_C9900007362
U$1: GAMEBOY_COLOR_DPAD_MEMBRANE
U$2: GAMEBOY_COLOR_START_SELECT_MEMBRANE
USB1: USB-C-SMD_TYPE-611-T3-W

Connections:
1: L1.1, U5.8, U5.9
2: L1.2, U5.6, U5.7
8: R31.2, U6.8
A5: R23.1, USB1.A5
B5: R24.1, USB1.B5
DATA_N: USB1.A7, USB1.B7
DATA_P: USB1.A6, USB1.B6
EN: R12.1, U1.5
FB: R21.1, R22.2, U5.3
INTN: R15.2, U2.22
PROG: R7.1, U4.5
RSTN: R16.2, U2.23
SCL: CN2.4, R13.2, U1.2, U2.19, U3.7
SDA: CN2.3, R14.2, U1.3, U2.20, U3.8
STAT: LED1.2, U4.1
a: H1.1, U1.7
b: H1.2, U1.9
b-line: R4.2, SW2.1, SW2.3, U2.11
battery_measurement: C1.1, R1.1, R2.2
boost_en: R27.2, TP2.1, U5.12
cs-2: R30.2, U6.2
down: R8.2, SW5.1, SW5.3, U2.6
gnd: C1.2, C2.2, C3.2, C4.2, C5.2, C6.2, C7.2, C8.2, C9.2, C10.2, C11.2, C12.2, C13.2, C14.2, CN1.2, CN1.3, CN1.4, CN2.1, CN2.5, CN2.6, R1.2, R7.2, R21.2, R23.2, R24.2, SW1.2, SW1.4, SW2.2, SW2.4, SW3.2, SW3.4, SW4.2, SW4.4, SW5.2, SW5.4, SW6.2, SW6.4, SW7.2, SW7.4, SW8.2, SW8.4, SW9.2, SW9.4, SW10.2, SW10.4, SW11.2, SW11.3, SW11.4, SW12.2, SW12.3, SW12.4, TP3.1, TP5.1, U1.4, U1.8, U2.9, U2.18, U2.24, U2.25, U3.1, U3.4, U3.6, U3.9, U4.2, U5.2, U5.13, U5.15, U6.6, U6.G, USB1.17, USB1.18, USB1.19, USB1.20, USB1.A1B12, USB1.B1A12
hv: C2.1, U1.1
left: R9.2, SW6.1, SW6.3, U2.7
line: R3.2, SW1.1, SW1.3, U2.10
nALRT: R18.1, U2.4, U3.5
pos: LED1.1, R17.2
right: R10.2, SW7.1, SW7.3, U2.8
select: R19.2, SW9.1, SW9.3, U2.2
start: R20.2, SW10.1, SW10.3, U2.1
uSD-1: R32.2, U6.1
up: R11.2, SW8.1, SW8.3, U2.5
vbat: C5.1, C6.1, C8.1, C9.1, C12.1, CN1.1, R2.1, R27.1, TP4.1, TP6.1, U3.2, U3.3, U4.3, U5.1, U5.10, U5.11
vbus: C7.1, D1.2, R17.1, U4.4, USB1.A4B9, USB1.A9B4
vcc_3v3: C3.1, C4.1, C13.1, C14.1, CN2.2, R3.1, R4.1, R5.1, R6.1, R8.1, R9.1, R10.1, R11.1, R12.2, R13.1, R14.1, R15.1, R16.1, R18.2, R19.1, R20.1, R25.1, R26.1, R30.1, R31.1, R32.1, U1.6, U1.10, U2.21, U6.4
vcc_5v: C10.1, C11.1, D1.1, R22.1, TP1.1, U5.4, U5.5
vol_down: R25.2, SW11.1, U2.15
vol_up: R26.2, SW12.1, U2.14
x_y_btns-a-line: R5.2, SW3.1, SW3.3, U2.12
x_y_btns-b-line: R6.2, SW4.1, SW4.3, U2.13

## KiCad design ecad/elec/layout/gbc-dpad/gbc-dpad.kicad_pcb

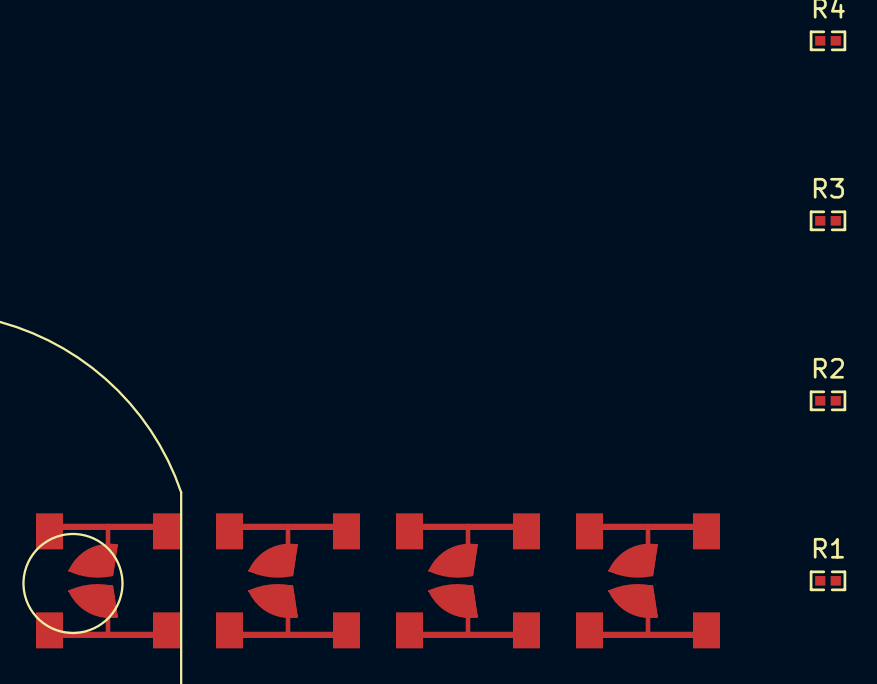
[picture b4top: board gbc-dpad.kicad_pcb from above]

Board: 2 copper layers, 9 parts (0 on the bottom side), 6 nets, no tracks yet.

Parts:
MECH1: GAMEBOY_COLOR_DPAD_MEMBRANE
R1, R2, R3, R4: 10kΩ ±5%; R0402
SW1, SW2, SW3, SW4: GBC_DPAD_BUTTON

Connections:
contact_in: R1.2, SW1.1, SW1.3
hv: R1.1, R2.1, R3.1, R4.1
left_button-out-contact_in: R2.2, SW2.1, SW2.3
lv: SW1.2, SW1.4, SW2.2, SW2.4, SW3.2, SW3.4, SW4.2, SW4.4
right_button-out-contact_in: R3.2, SW3.1, SW3.3
up_button-out-contact_in: R4.2, SW4.1, SW4.3

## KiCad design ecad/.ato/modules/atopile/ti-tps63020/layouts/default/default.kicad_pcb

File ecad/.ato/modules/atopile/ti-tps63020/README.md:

# Texas Instruments TPS63020 High Efficiency Single Inductor Buck-boost Converter

## Overview

The TPS63020 is a high-efficiency, single-inductor buck-boost converter with 4-A switches. It provides a power supply solution with a 1.8V to 5.5V input voltage range and delivers output voltages between 1.2V to 5.5V. This makes it ideal for battery-powered applications where the input voltage can be above, below, or equal to the output voltage.

## Key Features

- Input voltage range: 1.8V to 5.5V
- Output voltage range: 1.2V to 5.5V (adjustable)
- Output current: up to 3A (buck mode), 2A (boost mode)
- Switching frequency: 2.4MHz typical
- Efficiency: up to 95%
- Small solution size with integrated switches
- Power good output

## Usage

```ato

import ElectricPower

from "atopile/ti-tps63020/ti-tps63020.ato" import TPS63020_driver

module Usage:
    """
    Example usage of the TPS63020 buck-boost converter
    """

    # Power rails
    power_in = new ElectricPower
    power_3v3 = new ElectricPower

    # Configure input power (e.g., from battery)
    assert power_in.voltage within 2.5V to 5V

    # Configure output power
    assert power_3v3.voltage within 3.3V +/- 5%

    # Create buck-boost converter
    converter = new TPS63020_driver

    # Connect power
    power_in ~> converter ~> power_3v3
```

## Implementation Details

This package includes:
- Automatic calculation of feedback resistor values
- Proper decoupling capacitors on input and output
- Inductor selection with appropriate current rating
- Power good pullup resistor
- Compensation network calculations

The module automatically handles:
- Right half-plane zero frequency verification for stable operation
- Peak inductor current calculations
- Proper component sizing based on voltage and current requirements

## Contributing

Contributions to this package are welcome via pull requests on the GitHub repository.

## License

This atopile package is provided under the [MIT License](https://opensource.org/license/mit/).

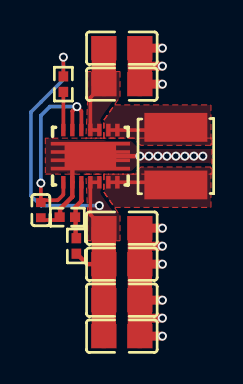
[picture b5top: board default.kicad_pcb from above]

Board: 2 copper layers, 12 parts (0 on the bottom side), 9 nets.

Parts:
C1, C2: 10µF ±10%; C0805
C3, C4, C5, C6: 22µF ±20%; C0805
C7: 100nF ±10%; C0402
L1: L 1µH ±20%; IND-SMD_L4.0-W4.0
R1: 102kΩ ±1%; R0402
R2: 34.8kΩ ±1%; R0402
R3: 1MΩ ±1%; R0402
U1: VSON-14_L4.0-W3.0-P0.50-BL-EP_TI_DSJ

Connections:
6: L1.2, U1.6, U1.7
8: L1.1, U1.8, U1.9
PG: R3.1, U1.14
hv: C7.1, U1.1, U1.12, U1.13
input_decoupling_capacitor[1]-power-hv: C1.1, C2.1, U1.10, U1.11
input_decoupling_capacitor[1]-power-lv: C1.2, C2.2, U1.2, U1.15
output_decoupling_capacitor[3]-power-hv: C3.1, C4.1, C5.1, C6.1, R1.1, R3.2, U1.4, U1.5
output_decoupling_capacitor[3]-power-lv: C3.2, C4.2, C5.2, C6.2, R2.2
ref_out-hv: R1.2, R2.1, U1.3

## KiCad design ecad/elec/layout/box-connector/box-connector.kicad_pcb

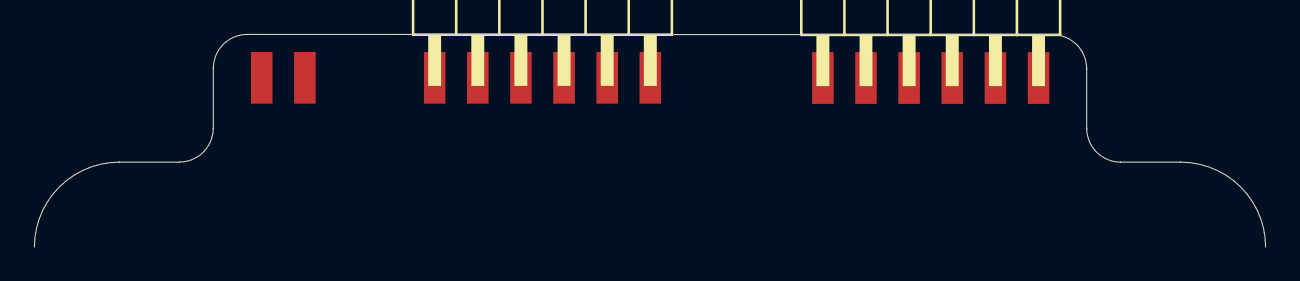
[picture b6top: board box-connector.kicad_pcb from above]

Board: 2 copper layers, 3 parts (1 on the bottom side), 3 nets, no tracks yet.

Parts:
J1, J2: 2X06_EDGE_REVERSED
U4: 2X02_EDGE_REVERSED

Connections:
hv: J1.11, J1.12, J2.11, J2.12
lv: J1.9, J1.10, J2.9, J2.10, U4.2, U4.3
power_5v-hv: U4.1, U4.4

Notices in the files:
README.md:
This project is licensed under the terms in [LICENSE](./LICENSE).
